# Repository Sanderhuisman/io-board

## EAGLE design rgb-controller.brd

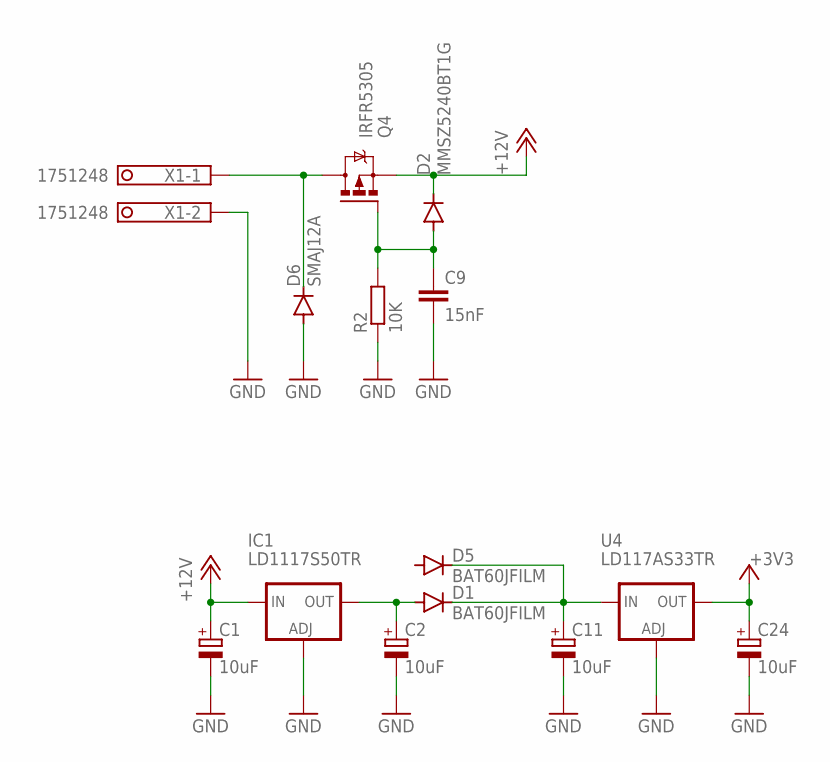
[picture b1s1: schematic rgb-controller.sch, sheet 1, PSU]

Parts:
C1, C2, C11, C24: 10uF; SMC_C
C9: 15nF; C0805
D1, D5: BAT60JFILM; SOD323-W
D2: MMSZ5240BT1G; SOD123
D6: SMAJ12A; DO-214AC
IC1: LD1117S50TR; SOT223
Q4: IRFR5305; D-PAK_TO252AA
R2: 10K; R0805
U4: LD117AS33TR; SOT223
X1: 1751248

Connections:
+3V3: C24.+, U4.4 (OUT); also elsewhere on the board
+12V: C1.+, D2.C, IC1.3 (IN), Q4.3 (S); also elsewhere on the board
GND: C1.-, C2.-, C9.2, C11.-, C24.-, D6.A, IC1.1 (ADJ), R2.1, U4.1 (ADJ), X1.2; also elsewhere on the board
unnamed: C2.+, D1.A, IC1.4 (OUT)
unnamed: C9.1, D2.A, Q4.1 (G), R2.2
unnamed: C11.+, D1.C, D5.C, U4.3 (IN)
VIN: D6.C, Q4.4 (D), X1.1

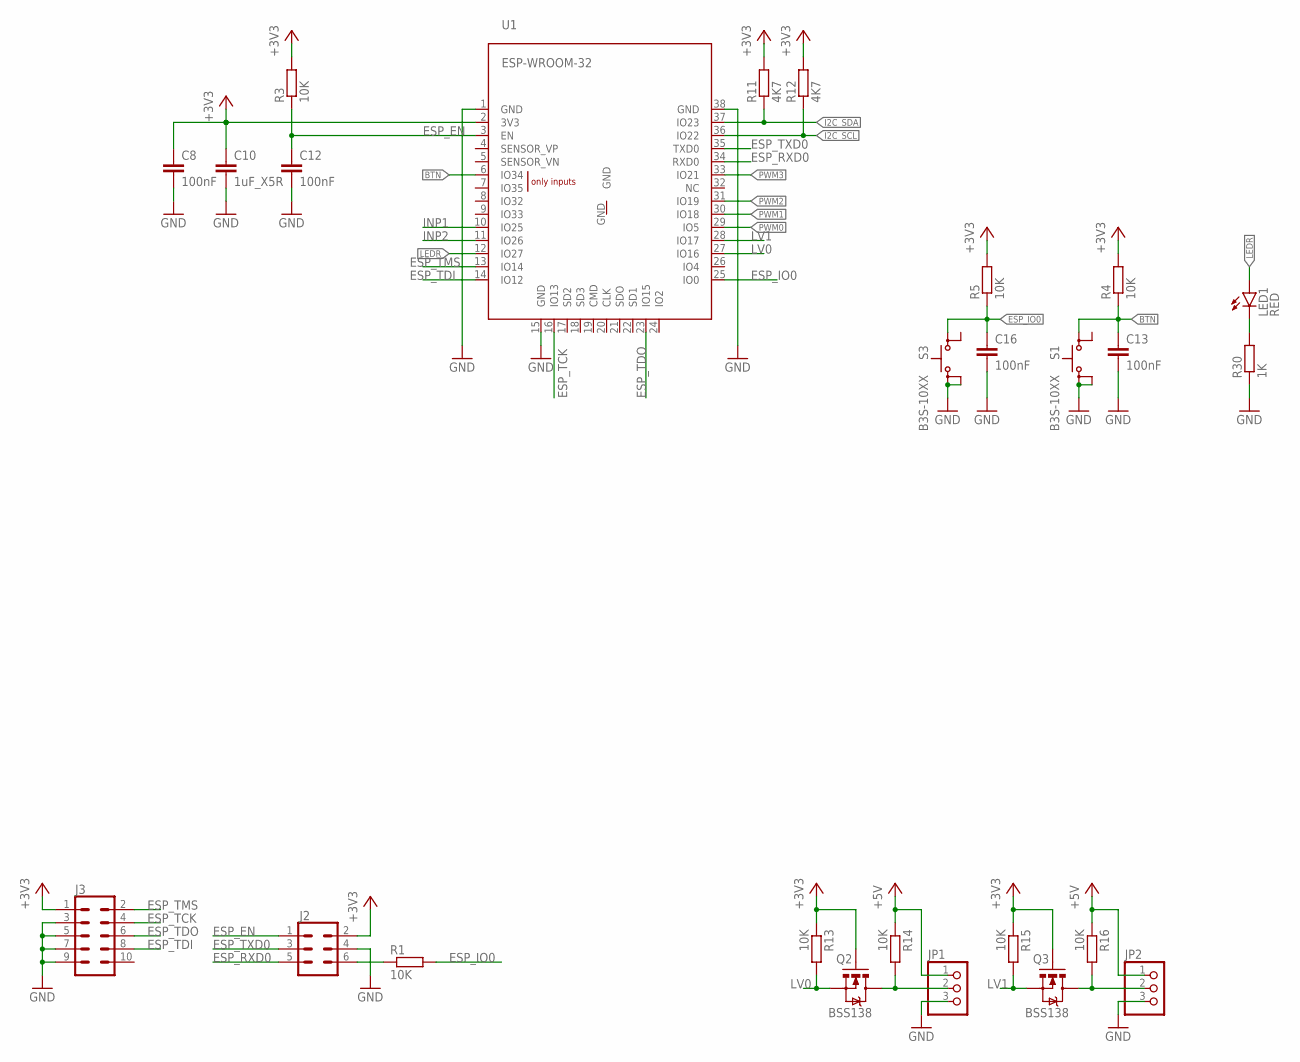
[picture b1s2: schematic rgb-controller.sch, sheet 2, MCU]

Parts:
C8, C12, C13, C16: 100nF; C0805
C10: 1uF_X5R; C0805
J2: CONN_03X2SHROUD; 2X3-SHROUDED
J3: CONN_05X2SHD; 2X5-SHROUDED
JP1, JP2: PINHD-1X3; 1X03
LED1: RED; CHIPLED_0805
Q2, Q3: BSS138; SOT23-3
R1, R3, R4, R5, R13, R14, R15, R16: 10K; R0805
R11, R12: 4K7; R0805
R30: 1K; R0805
S1, S3: B3S-10XX
U1: ESP-WROOM-32

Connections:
+3V3: C8.1, C10.1, J2.2, J3.1, Q2.1 (G), Q3.1 (G), R3.2, R4.2, R5.2, R11.2, R12.2, R13.1, R15.1, U1.2 (3V3); also elsewhere on the board
+5V: JP1.1, JP2.1, R14.1, R16.1; also elsewhere on the board
BTN: C13.1, R4.1, S1.1, U1.6 (IO34)
ESP_EN: C12.1, J2.1, R3.1, U1.3 (EN)
ESP_IO0: C16.1, R1.2, R5.1, S3.1, U1.25 (IO0)
ESP_RXD0: J2.5, U1.34 (RXD0)
ESP_TCK: J3.4, U1.16 (IO13)
ESP_TDI: J3.8, U1.14 (IO12)
ESP_TDO: J3.6, U1.23 (IO15)
ESP_TMS: J3.2, U1.13 (IO14)
ESP_TXD0: J2.3, U1.35 (TXD0)
GND: C8.2, C10.2, C12.2, C13.2, C16.2, J2.4, J3.3, J3.5, J3.7, J3.9, JP1.3, JP2.3, R30.2, S1.3 (S), S1.4 (S1), S3.3 (S), S3.4 (S1), U1.1 (GND), U1.15 (GND), U1.38 (GND); also elsewhere on the board
HV1: JP1.2, Q2.3 (D), R14.2
HV2: JP2.2, Q3.3 (D), R16.2
I2C_SCL: R12.1, U1.36 (IO22); also elsewhere on the board
I2C_SDA: R11.1, U1.37 (IO23); also elsewhere on the board
INP1: U1.10 (IO25); also elsewhere on the board
INP2: U1.11 (IO26); also elsewhere on the board
LEDR: LED1.A, U1.12 (IO27)
LV0: Q2.2 (S), R13.2, U1.27 (IO16)
LV1: Q3.2 (S), R15.2, U1.28 (IO17)
unnamed: J2.6, R1.1
unnamed: LED1.C, R30.1
PWM0: U1.29 (IO5); also elsewhere on the board
PWM1: U1.30 (IO18); also elsewhere on the board
PWM2: U1.31 (IO19); also elsewhere on the board
PWM3: U1.33 (IO21); also elsewhere on the board

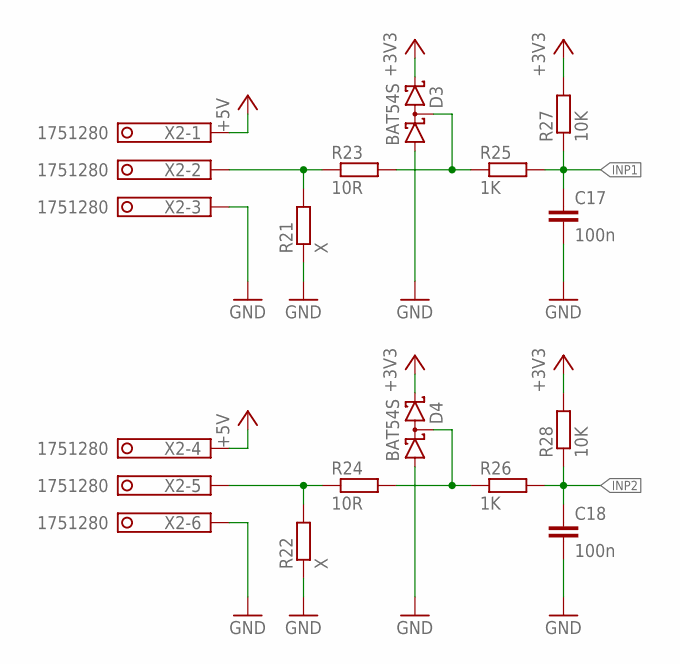
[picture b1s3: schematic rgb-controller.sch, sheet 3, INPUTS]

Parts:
C17, C18: 100n; C0805
D3, D4: BAT54S; SOT23
R21, R22: X; R0805
R23, R24: 10R; R0805
R25, R26: 1K; R0805
R27, R28: 10K; R0805
X2: 1751280

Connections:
+3V3: D3.2 (C2), D4.2 (C2), R27.2, R28.2; also elsewhere on the board
+5V: X2.1, X2.4; also elsewhere on the board
GND: C17.2, C18.2, D3.1 (A1), D4.1 (A1), R21.1, R22.1, X2.3, X2.6; also elsewhere on the board
INP1: C17.1, R25.2, R27.1; also elsewhere on the board
INP2: C18.1, R26.2, R28.1; also elsewhere on the board
unnamed: R22.2, R24.1, X2.5
unnamed: D3.3 (C1A2), R23.2, R25.1
unnamed: D4.3 (C1A2), R24.2, R26.1
unnamed: R21.2, R23.1, X2.2

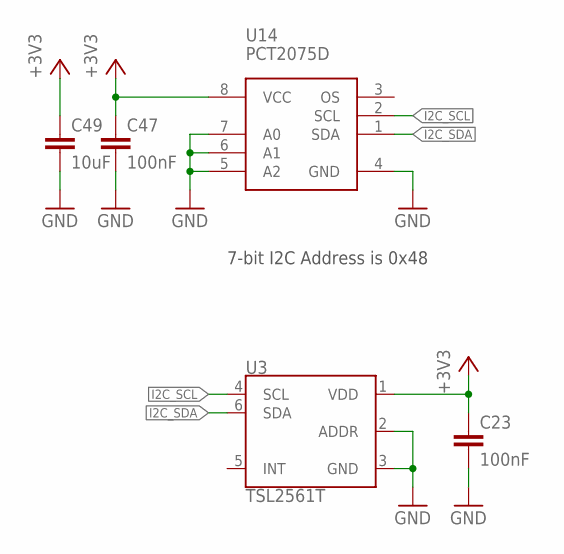
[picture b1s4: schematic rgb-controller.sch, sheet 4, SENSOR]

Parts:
C23, C47: 100nF; C0805
C49: 10uF; C0805
U3: TSL2561T; TMB-6
U14: PCT2075D; SOIC8_150MIL

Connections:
+3V3: C23.1, C47.1, C49.1, U3.1 (VDD), U14.8 (VCC); also elsewhere on the board
GND: C23.2, C47.2, C49.2, U3.2 (ADDR), U3.3 (GND), U14.4 (GND), U14.5 (A2), U14.6 (A1), U14.7 (A0); also elsewhere on the board
I2C_SCL: U3.4 (SCL), U14.2 (SCL); also elsewhere on the board
I2C_SDA: U3.6 (SDA), U14.1 (SDA); also elsewhere on the board

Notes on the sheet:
7-bit I2C Address is 0x48

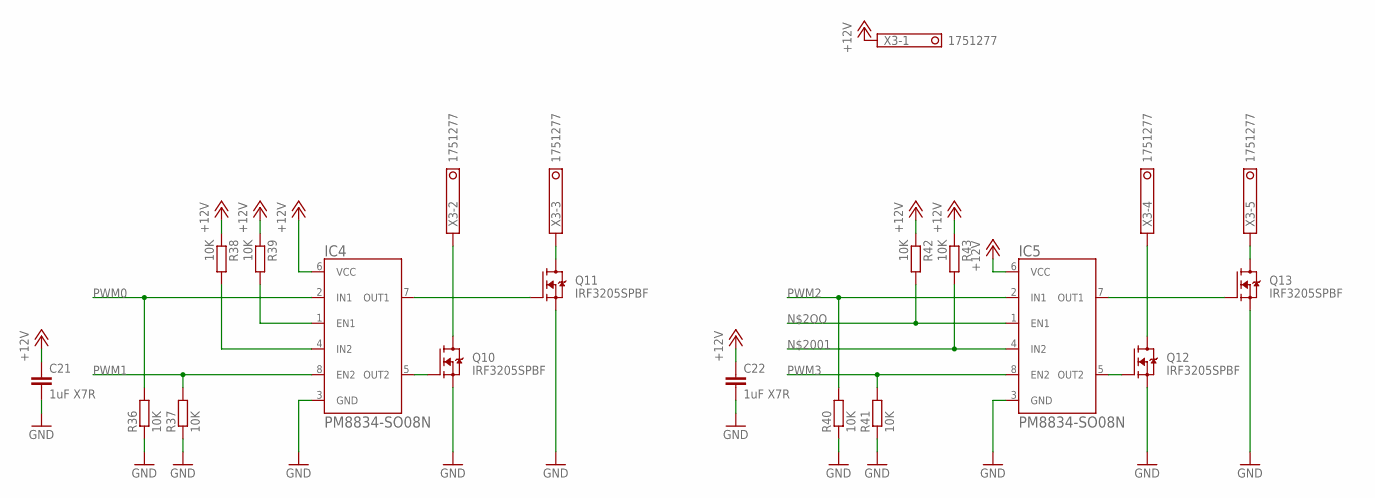
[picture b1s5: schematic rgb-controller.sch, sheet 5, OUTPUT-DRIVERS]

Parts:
C21, C22: 1uF X7R; C0805
IC4, IC5: PM8834-SO08N; SO08N
Q10, Q11, Q12, Q13: IRF3205SPBF; TRANS_IRF3205SPBF
R36, R37, R38, R39, R40, R41, R42, R43: 10K; R0805
X3: 1751277

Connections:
+12V: C21.1, C22.1, IC4.6 (VCC), IC5.6 (VCC), R38.2, R39.2, R42.2, R43.2, X3.1; also elsewhere on the board
GND: C21.2, C22.2, IC4.3 (GND), IC5.3 (GND), Q10.3 (S), Q11.3 (S), Q12.3 (S), Q13.3 (S), R36.2, R37.2, R40.2, R41.2; also elsewhere on the board
unnamed: IC5.1 (EN1), R42.1
unnamed: Q10.2 (D), X3.2
unnamed: IC4.1 (EN1), R39.1
unnamed: IC4.4 (IN2), R38.1
unnamed: IC4.7 (OUT1), Q11.1 (G)
unnamed: IC4.5 (OUT2), Q10.1 (G)
unnamed: Q11.2 (D), X3.3
unnamed: IC5.7 (OUT1), Q13.1 (G)
unnamed: IC5.5 (OUT2), Q12.1 (G)
unnamed: Q12.2 (D), X3.4
unnamed: Q13.2 (D), X3.5
unnamed: IC5.4 (IN2), R43.1
PWM0: IC4.2 (IN1), R36.1; also elsewhere on the board
PWM1: IC4.8 (EN2), R37.1; also elsewhere on the board
PWM2: IC5.2 (IN1), R40.1; also elsewhere on the board
PWM3: IC5.8 (EN2), R41.1; also elsewhere on the board

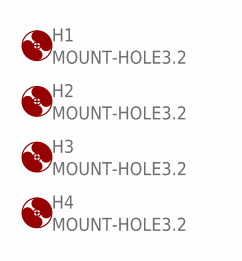
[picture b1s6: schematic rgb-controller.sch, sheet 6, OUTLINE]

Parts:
H1, H2, H3, H4: MOUNT-HOLE3.2; 3,2

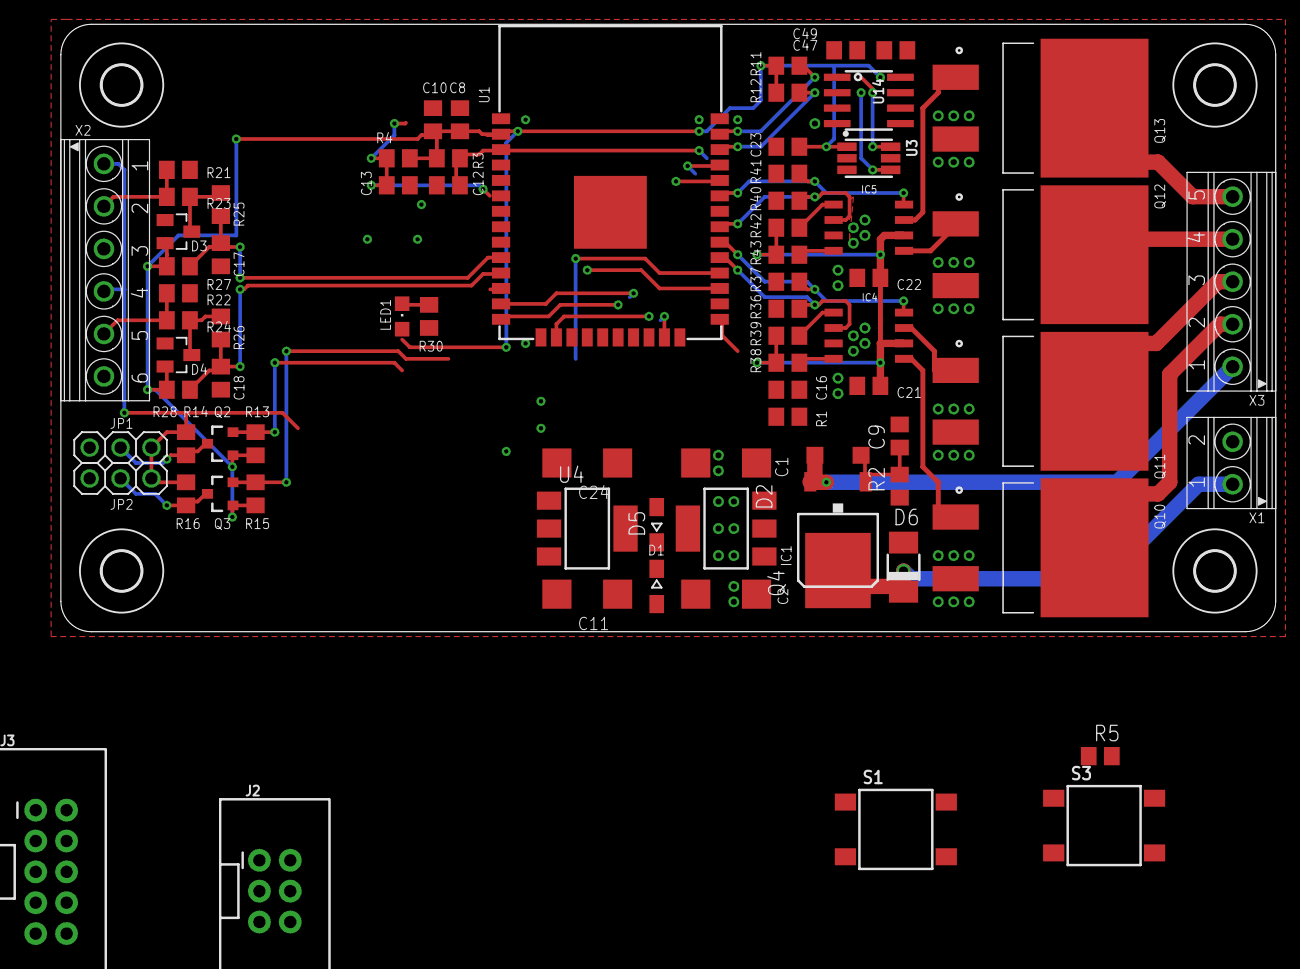
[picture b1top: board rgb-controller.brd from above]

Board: 2 copper layers, 100.0 x 50.0 mm, 79 parts (0 on the bottom side), 48 nets.

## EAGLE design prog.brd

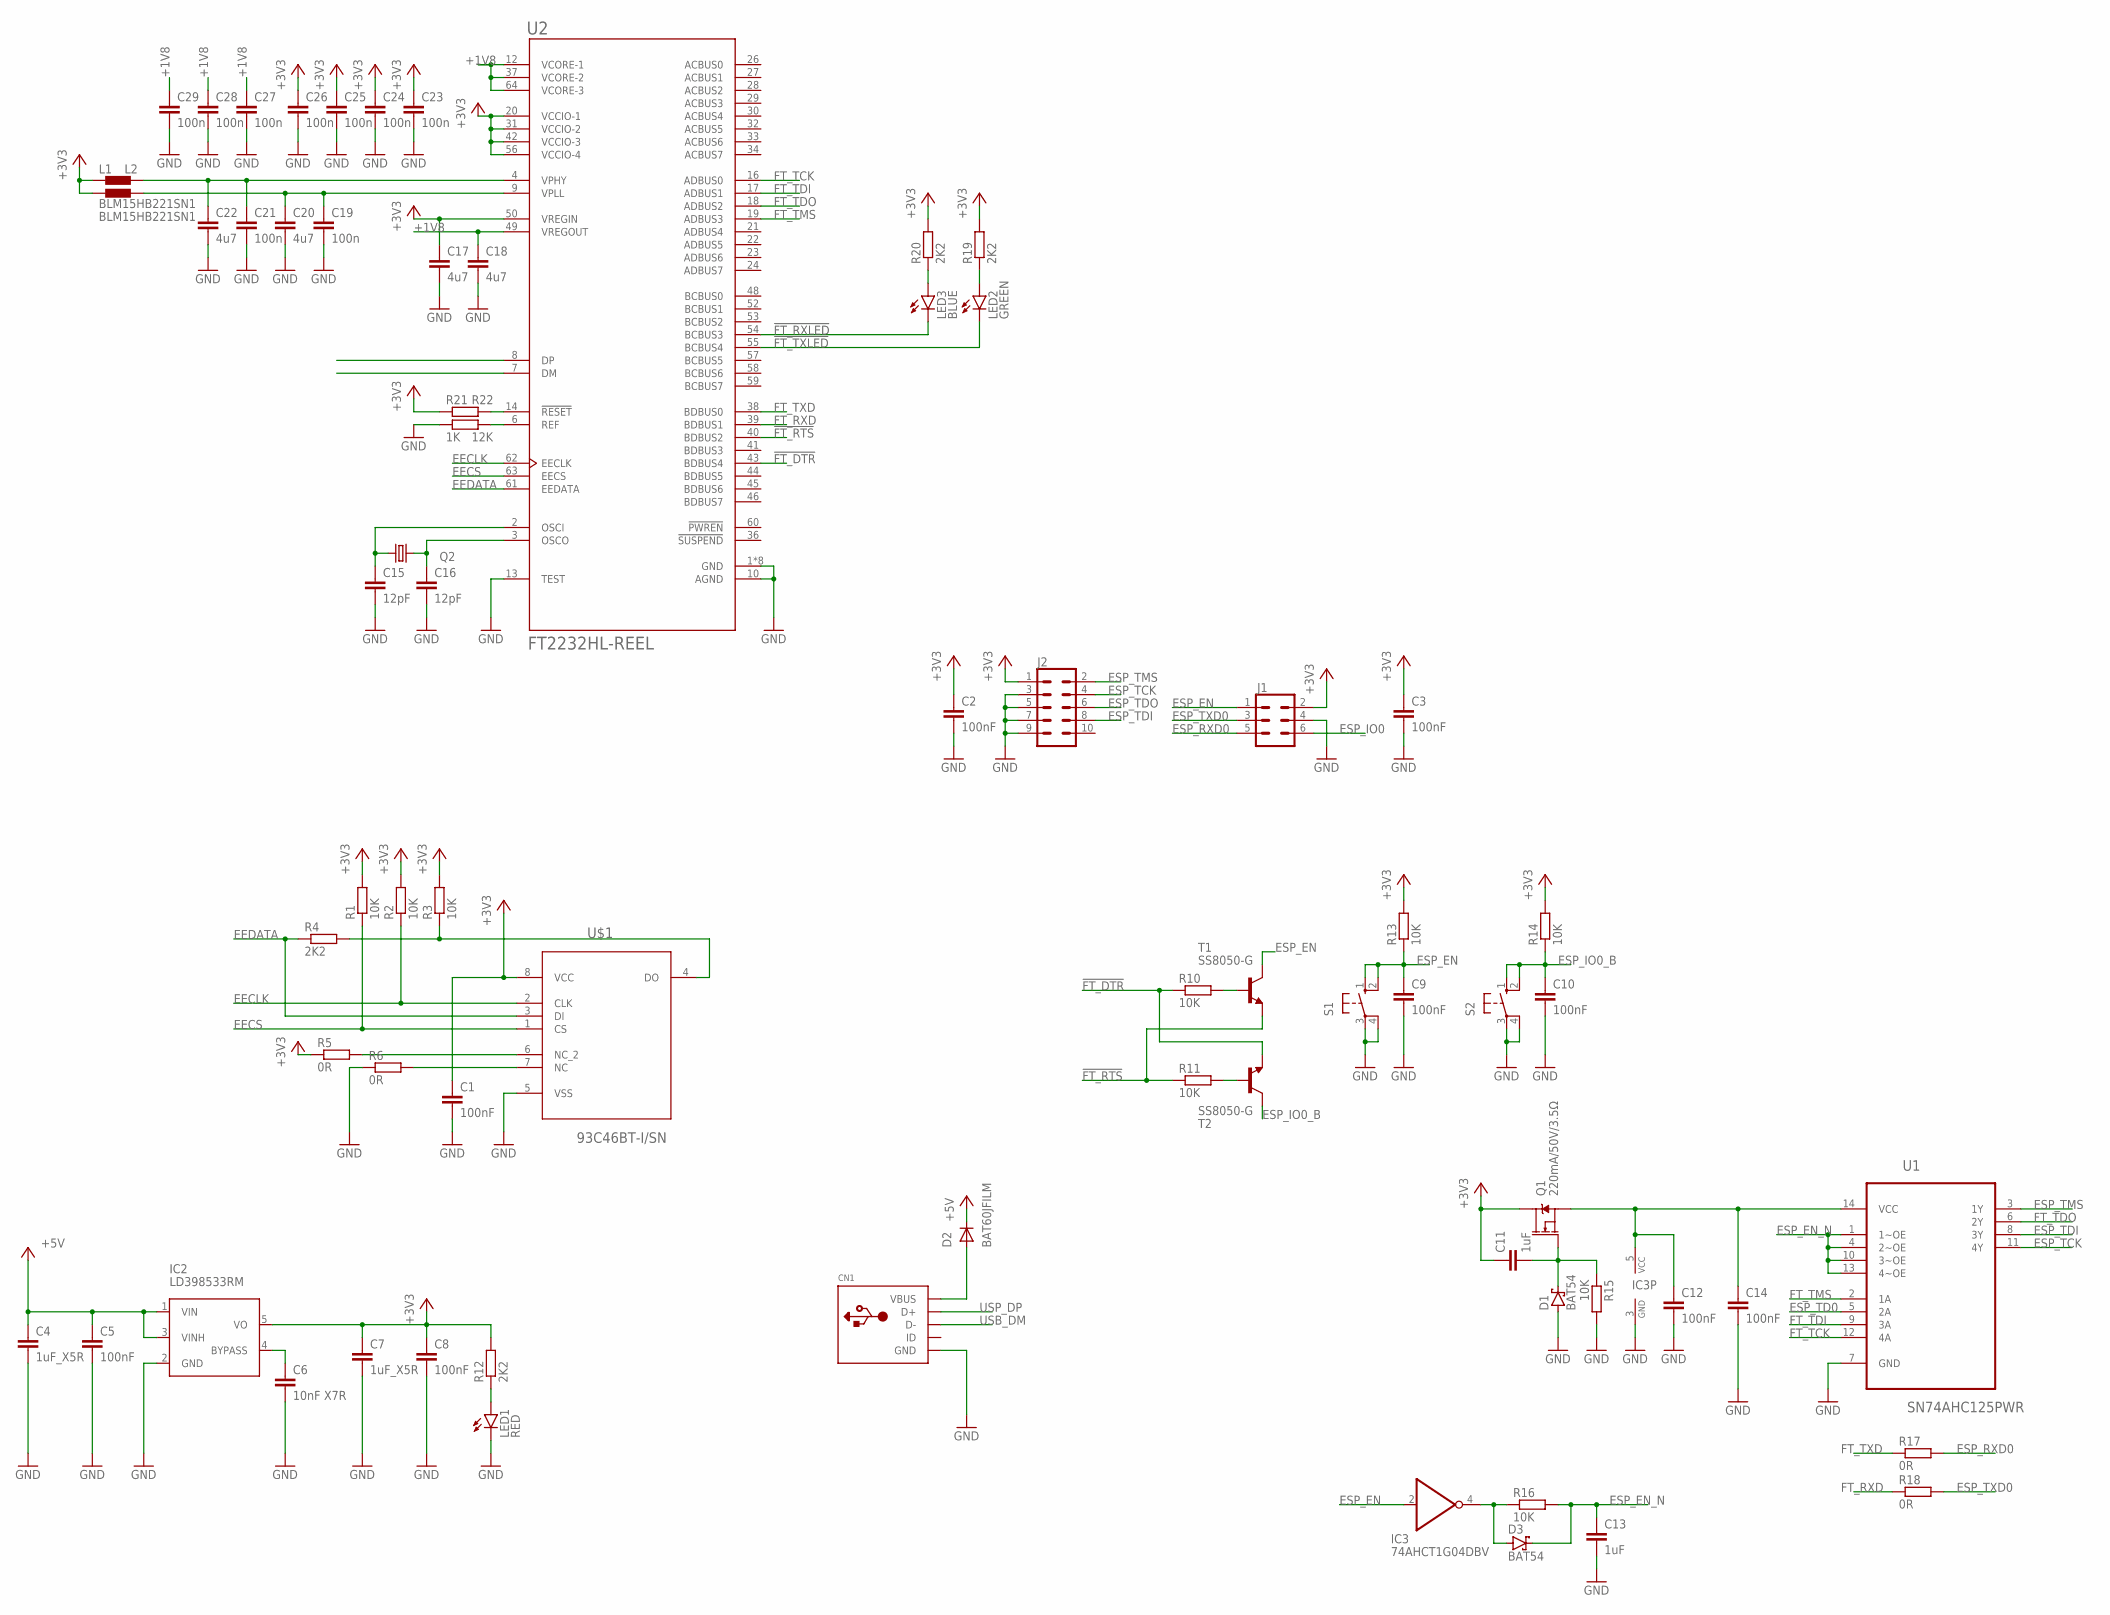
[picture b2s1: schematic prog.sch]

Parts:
C1, C2, C3, C5, C8, C9, C10, C12, C14: 100nF; C0805
C4, C7: 1uF_X5R; C0805
C6: 10nF X7R; C0805
C11, C13: 1uF; C0805
C15, C16: 12pF; C0805
C17, C18, C20, C22: 4u7; C0805
C19, C21, C23, C24, C25, C26, C27, C28, C29: 100n; C0805
CN1: USBMINIB; USB-MINIB
D1, D3: BAT54; SOT23
D2: BAT60JFILM; SOD323-W
IC2: LD398533RM; SOT23-5L
IC3: 74AHCT1G04DBV; SOT23-5
J1: CONN_03X2SHROUD; 2X3-SHROUDED
J2: CONN_05X2SHD; 2X5-SHROUDED
L1, L2: BLM15HB221SN1; 0402
LED1: RED; CHIP-LED0805
LED2: GREEN; CHIPLED_0805
LED3: BLUE; CHIPLED_0805
Q1: 220mA/50V/3.5Ω; SOT23-3
Q2: CRYSTALHC49UP; HC49UP
R1, R2, R3, R10, R11, R13, R14, R15, R16: 10K; R0805
R4, R12, R19, R20: 2K2; R0805
R5, R6, R17, R18: 0R; R0805
R21: 12K; R0805
R22: 1K; R0805
S1, S2: 10-XX; B3F-10XX
T1, T2: SS8050-G; SOT23-BEC
U1: SN74AHC125PWR; SOP65P640X120-14N
U2: FT2232HL-REEL; QFP50P1200X1200X160-64N
U$1: 93C46BT-I/SN; SOIC127P600X175-8N

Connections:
!FT_DTR: R10.1, T2.E, U2.43 (BDBUS4)
!FT_RTS: R11.1, T1.E, U2.40 (BDBUS2)
!FT_RXLED: LED3.C, U2.54 (BCBUS3)
!FT_TXLED: LED2.C, U2.55 (BCBUS4)
+1V8: C18.1, C27.1, C28.1, C29.1, U2.12 (VCORE-1), U2.37 (VCORE-2), U2.49 (VREGOUT), U2.64 (VCORE-3)
+3V3: C1.1, C2.1, C3.1, C7.1, C8.1, C11.1, C17.1, C23.1, C24.1, C25.1, C26.1, IC2.5 (VO), J1.2, J2.1, L1.1, L2.1, Q1.3 (D), R1.2, R2.2, R3.2, R5.1, R12.2, R13.2, R14.2, R19.2, R20.2, R22.1, U2.20 (VCCIO-1), U2.31 (VCCIO-2), U2.42 (VCCIO-3), U2.50 (VREGIN), U2.56 (VCCIO-4), U$1.8 (VCC)
+5V: C4.1, C5.1, D2.C, IC2.1 (VIN), IC2.3 (VINH)
EECLK: R2.1, U2.62 (EECLK), U$1.2 (CLK)
EECS: R1.1, U2.63 (EECS), U$1.1 (CS)
EEDATA: R4.1, U2.61 (EEDATA), U$1.3 (DI)
ESP_EN: C9.1, IC3.2 (I), J1.1, R13.1, S1.1 (S), S1.2 (S1), T1.C
ESP_EN_N: C13.1, D3.3 (C), R16.2, U1.1 (1~OE), U1.4 (2~OE), U1.10 (3~OE), U1.13 (4~OE)
ESP_IO0: J1.6
ESP_IO0_B: C10.1, R14.1, S2.1 (S), S2.2 (S1), T2.C
ESP_RXD0: J1.5, R17.2
ESP_TCK: J2.4, U1.11 (4Y)
ESP_TD0: U1.5 (2A)
ESP_TDI: J2.8, U1.8 (3Y)
ESP_TDO: J2.6
ESP_TMS: J2.2, U1.3 (1Y)
ESP_TXD0: J1.3, R18.2
FT_RXD: R18.1, U2.39 (BDBUS1)
FT_TCK: U1.12 (4A), U2.16 (ADBUS0)
FT_TDI: U1.9 (3A), U2.17 (ADBUS1)
FT_TDO: U1.6 (2Y), U2.18 (ADBUS2)
FT_TMS: U1.2 (1A), U2.19 (ADBUS3)
FT_TXD: R17.1, U2.38 (BDBUS0)
GND: C1.2, C2.2, C3.2, C4.2, C5.2, C6.2, C7.2, C8.2, C9.2, C10.2, C12.2, C13.2, C14.2, C15.2, C16.2, C17.2, C18.2, C19.2, C20.2, C21.2, C22.2, C23.2, C24.2, C25.2, C26.2, C27.2, C28.2, C29.2, CN1.GND, D1.1 (A), IC2.2 (GND), IC3.3 (GND), J1.4, J2.3, J2.5, J2.7, J2.9, LED1.C, R6.1, R15.2, R21.1, S1.3, S1.4 (P1), S2.3, S2.4 (P1), U1.7 (GND), U2.1 (GND), U2.5 (GND), U2.10 (AGND), U2.11 (GND), U2.13 (TEST), U2.15 (GND), U2.25 (GND), U2.35 (GND), U2.47 (GND), U2.51 (GND), U$1.5 (VSS)
unnamed: R5.2, U$1.6 (NC_2)
unnamed: R6.2, U$1.7 (NC)
unnamed: R3.1, R4.2, U$1.4 (DO)
unnamed: LED1.A, R12.1
unnamed: C11.2, D1.3 (C), Q1.1 (G), R15.1
unnamed: D3.1 (A), IC3.4 (O), R16.1
unnamed: C12.1, C14.1, IC3.5 (VCC), Q1.2 (S), U1.14 (VCC)
unnamed: LED3.A, R20.1
unnamed: LED2.A, R19.1
unnamed: C15.1, Q2.1, U2.2 (OSCI)
unnamed: C16.1, Q2.2, U2.3 (OSCO)
unnamed: R22.2, U2.14 (!RESET)
unnamed: R21.2, U2.6 (REF)
unnamed: C19.1, C20.1, L2.2, U2.9 (VPLL)
unnamed: C21.1, C22.1, L1.2, U2.4 (VPHY)
unnamed: R10.2, T1.B
unnamed: R11.2, T2.B
unnamed: C6.1, IC2.4 (BYPASS)
USB_DM: CN1.D-
USP_DP: CN1.D+
VBUS1: CN1.VBUS, D2.A

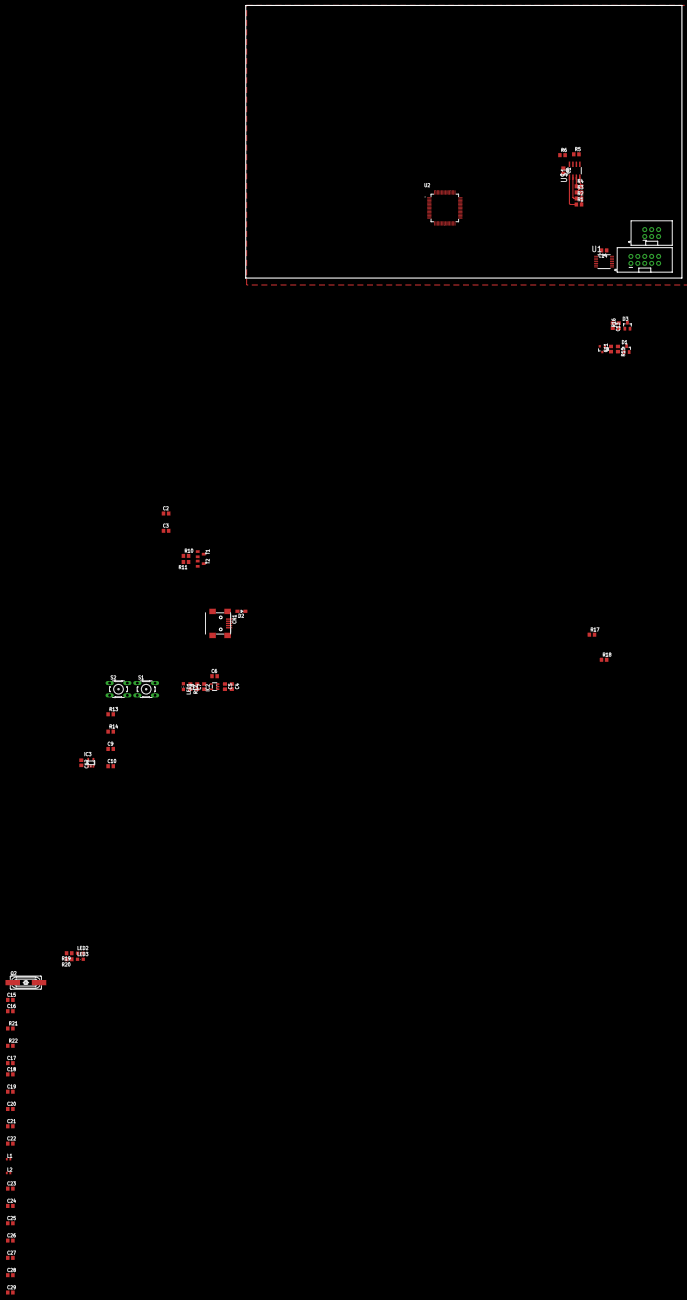
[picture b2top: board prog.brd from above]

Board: 2 copper layers, 160.0 x 100.0 mm, 70 parts (0 on the bottom side), 44 nets.

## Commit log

2018-12-16 Initial project
2018-12-16 Outline, mounting holes and groundplanes
2018-12-16 Added initial components
2018-12-18 Update :)
2018-12-18 layouting
2018-12-25 added level shifters
2018-12-26 Removed sensors
2018-12-28 P1 port and layouting
2019-01-02 Updatesss
2019-01-02 Layout
2019-01-02 All routed
2019-01-05 Added light sensor
2019-01-06 Removed temp alert signal
2019-01-06 Initial prog board
2019-01-08 Replaced usb chip by connector
2019-01-09 work on programmer board
2019-11-03 eagle

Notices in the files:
parts and their libraries:
SparkFun-Connectors: Licensing: Creative Commons ShareAlike 4.0 International - https://creativecommons.org/licenses/by-sa/4.0
